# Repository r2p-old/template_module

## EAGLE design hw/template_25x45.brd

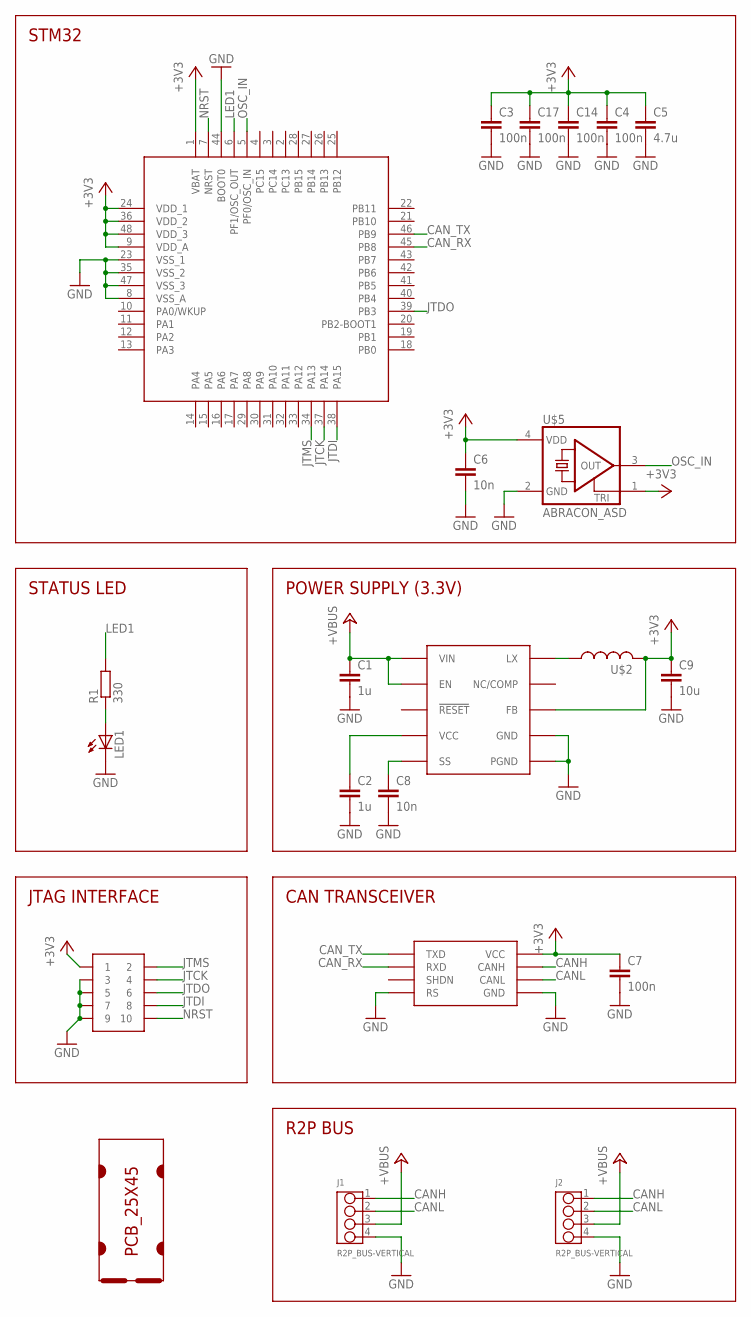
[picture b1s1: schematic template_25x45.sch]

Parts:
C1: 1u; C1206
C2: 1u; C0603
C3, C4, C7, C14, C17: 100n; C0603
C5: 4.7u; C0805
C6, C8: 10n; C0603
C9: 10u; C0805
J1, J2: R2P_BUS-VERTICAL; OPL-EAGLE-LIBRARY_4P-2.0
LED1: LED0805; CHIPLED_0805
R1: 330; R0603
SOT1: MAX3051EKA; SOT23-8L
U$1: PCB_25X45; 25X45
U$2: LPS4018; COILCRAFT_LPS4018
U$3: MAX17501; TDFN-10
U$4: JTAG-TH; SAMTEC_FTSH-105-TH
U$5: ABRACON_ASD; ABRACON_2.5X2
U$6: STM32F303CTX; LQFP48

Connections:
+3V3: C3.1, C4.1, C5.1, C6.1, C7.1, C9.1, C14.1, C17.1, SOT1.3 (VCC), U$2.P$2 (2), U$3.P$5 (FB), U$4.1, U$5.1 (TRI), U$5.4 (VDD), U$6.1 (VBAT), U$6.9 (VDD_A), U$6.24 (VDD_1), U$6.36 (VDD_2), U$6.48 (VDD_3)
+VBUS: C1.1, J1.3, J2.3, U$3.P$2 (VIN), U$3.P$3 (EN)
CANH: J1.1, J2.1, SOT1.7 (CANH)
CANL: J1.2, J2.2, SOT1.6 (CANL)
CAN_RX: SOT1.4 (RXD), U$6.45 (PB8)
CAN_TX: SOT1.1 (TXD), U$6.46 (PB9)
GND: C1.2, C2.2, C3.2, C4.2, C5.2, C6.2, C7.2, C8.2, C9.2, C14.2, C17.2, J1.4, J2.4, LED1.C, SOT1.2 (GND), SOT1.8 (RS), U$3.P$1 (PGND), U$3.P$9 (GND), U$3.P$11 (PGND), U$4.3, U$4.5, U$4.7, U$4.9, U$5.2 (GND), U$6.8 (VSS_A), U$6.23 (VSS_1), U$6.35 (VSS_2), U$6.44 (BOOT0), U$6.47 (VSS_3)
JTCK: U$4.4, U$6.37 (PA14)
JTDI: U$4.8, U$6.38 (PA15)
JTDO: U$4.6, U$6.39 (PB3)
JTMS: U$4.2, U$6.34 (PA13)
LED1: R1.2, U$6.6 (PF1/OSC_OUT)
unnamed: U$2.P$1 (1), U$3.P$10 (LX)
unnamed: LED1.A, R1.1
unnamed: C2.1, U$3.P$4 (VCC)
unnamed: C8.1, U$3.P$6 (SS)
NRST: U$4.10, U$6.7 (NRST)
OSC_IN: U$5.3 (OUT), U$6.5 (PF0/OSC_IN)

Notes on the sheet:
STM32
STATUS LED
JTAG INTERFACE
POWER SUPPLY (3.3V)
CAN TRANSCEIVER
R2P BUS

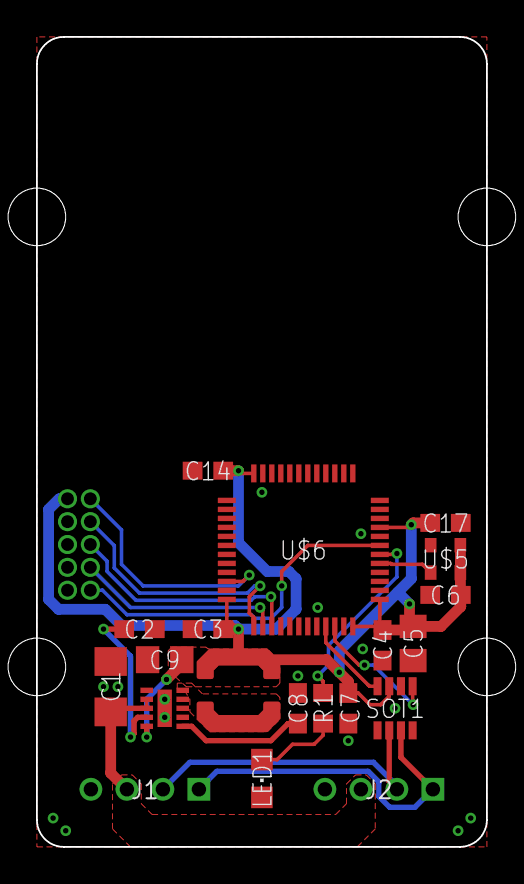
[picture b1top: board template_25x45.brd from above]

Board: 2 copper layers, 25.0 x 45.0 mm, 22 parts (0 on the bottom side), 18 nets.

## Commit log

2014-06-11 updated to STM32F303 family
2014-06-23 Added makefile for quicker gerber generation
2014-07-11 added 50x45mm template
2014-12-02 added missing values
2014-12-16 small fixes for production
2015-01-28 Added logo to bottom silkscreen
2015-01-28 Added Makefile
2015-01-28 Small layout improvements
2015-01-28 Template with 5V supply
2015-01-28 Cosmetic only
2015-01-31 Updated datasheets
2015-01-31 Updated to R2P Eagle libraries
2015-01-31 Approved DRU false warnings
2015-02-09 Updated keepout
